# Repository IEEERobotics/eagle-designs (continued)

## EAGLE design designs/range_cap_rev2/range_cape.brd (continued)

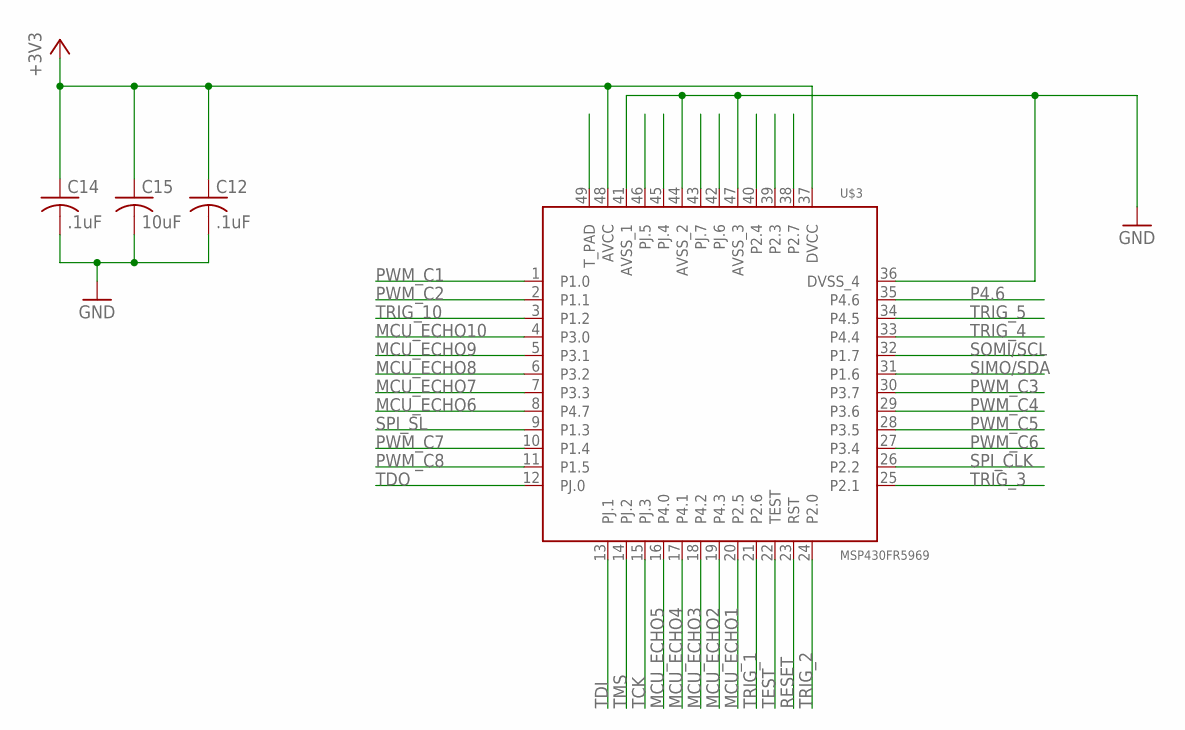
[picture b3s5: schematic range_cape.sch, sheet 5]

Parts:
C12, C14: .1uF; C0805
C15: 10uF; C0805
U$3: MSP430FR5969; QFN50P700X700X100-49N

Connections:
+3V3: C12.1, C14.1, C15.1, U$3.37 (DVCC), U$3.48 (AVCC); also elsewhere on the board
GND: C12.2, C14.2, C15.2, U$3.36 (DVSS_4), U$3.41 (AVSS_1), U$3.44 (AVSS_2), U$3.47 (AVSS_3); also elsewhere on the board
MCU_ECHO1: U$3.20 (P2.5); also elsewhere on the board
MCU_ECHO2: U$3.19 (P4.3); also elsewhere on the board
MCU_ECHO3: U$3.18 (P4.2); also elsewhere on the board
MCU_ECHO4: U$3.17 (P4.1); also elsewhere on the board
MCU_ECHO5: U$3.16 (P4.0); also elsewhere on the board
MCU_ECHO6: U$3.8 (P4.7); also elsewhere on the board
MCU_ECHO7: U$3.7 (P3.3); also elsewhere on the board
MCU_ECHO8: U$3.6 (P3.2); also elsewhere on the board
MCU_ECHO9: U$3.5 (P3.1); also elsewhere on the board
MCU_ECHO10: U$3.4 (P3.0); also elsewhere on the board
P2.3: U$3.39 (P2.3)
P2.4: U$3.40 (P2.4)
P2.7: U$3.38 (P2.7)
P4.6: U$3.35 (P4.6)
PWM_C1: U$3.1 (P1.0); also elsewhere on the board
PWM_C2: U$3.2 (P1.1); also elsewhere on the board
PWM_C3: U$3.30 (P3.7); also elsewhere on the board
PWM_C4: U$3.29 (P3.6); also elsewhere on the board
PWM_C5: U$3.28 (P3.5); also elsewhere on the board
PWM_C6: U$3.27 (P3.4); also elsewhere on the board
PWM_C7: U$3.10 (P1.4); also elsewhere on the board
PWM_C8: U$3.11 (P1.5); also elsewhere on the board
RESET: U$3.23 (RST); also elsewhere on the board
SIMO/SDA: U$3.31 (P1.6); also elsewhere on the board
SOMI/SCL: U$3.32 (P1.7); also elsewhere on the board
SPI_CLK: U$3.26 (P2.2); also elsewhere on the board
SPI_SL: U$3.9 (P1.3); also elsewhere on the board
TCK: U$3.15 (PJ.3); also elsewhere on the board
TDI: U$3.13 (PJ.1); also elsewhere on the board
TDO: U$3.12 (PJ.0); also elsewhere on the board
TEST: U$3.22 (TEST); also elsewhere on the board
TMS: U$3.14 (PJ.2); also elsewhere on the board
TRIG_1: U$3.21 (P2.6); also elsewhere on the board
TRIG_2: U$3.24 (P2.0); also elsewhere on the board
TRIG_3: U$3.25 (P2.1); also elsewhere on the board
TRIG_4: U$3.33 (P4.4); also elsewhere on the board
TRIG_5: U$3.34 (P4.5); also elsewhere on the board
TRIG_6: U$3.42 (PJ.6); also elsewhere on the board
TRIG_7: U$3.43 (PJ.7); also elsewhere on the board
TRIG_8: U$3.45 (PJ.4); also elsewhere on the board
TRIG_9: U$3.46 (PJ.5); also elsewhere on the board
TRIG_10: U$3.3 (P1.2); also elsewhere on the board
T_PAD: U$3.49 (T_PAD)

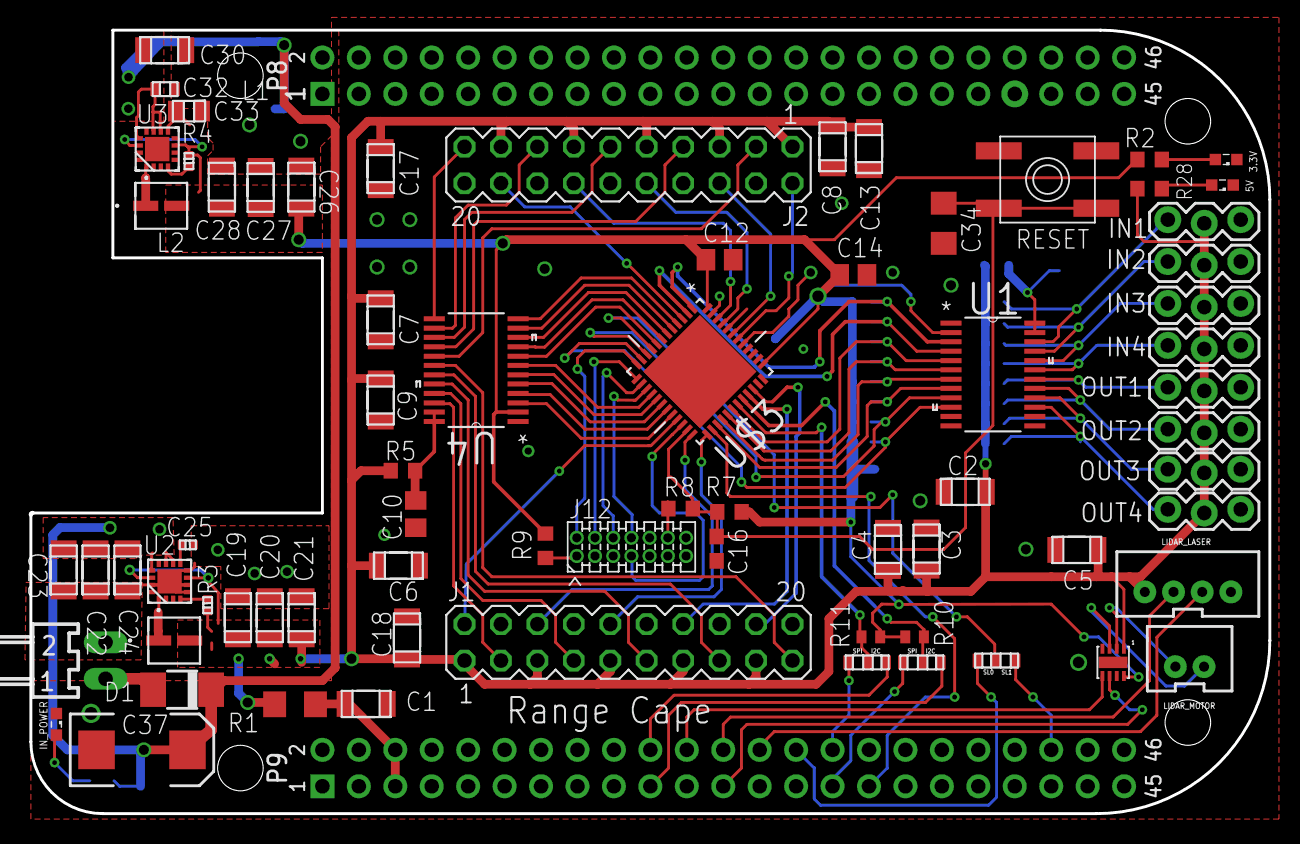
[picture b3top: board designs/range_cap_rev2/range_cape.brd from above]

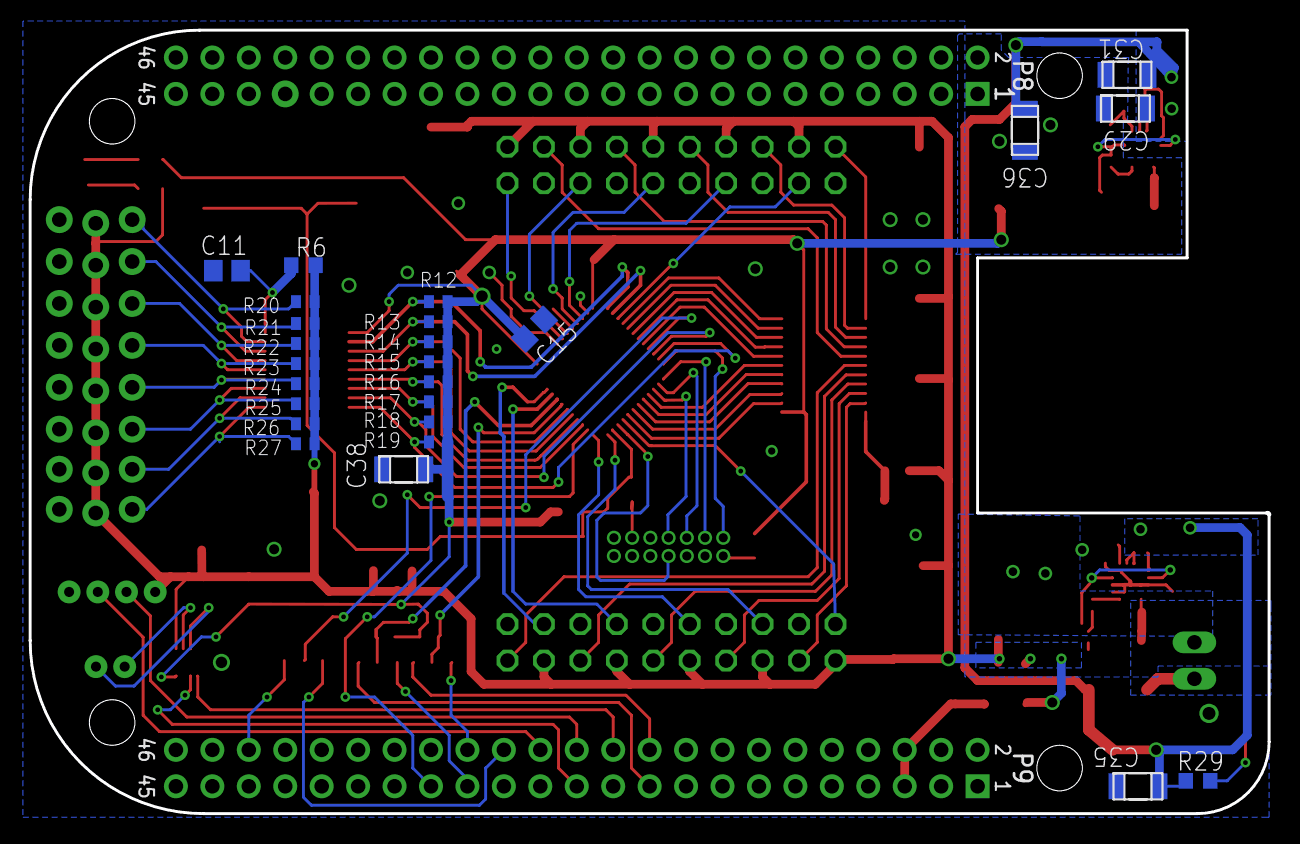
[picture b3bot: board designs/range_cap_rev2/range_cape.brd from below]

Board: 2 copper layers, 86.4 x 54.6 mm, 97 parts (25 on the bottom side), 87 nets.

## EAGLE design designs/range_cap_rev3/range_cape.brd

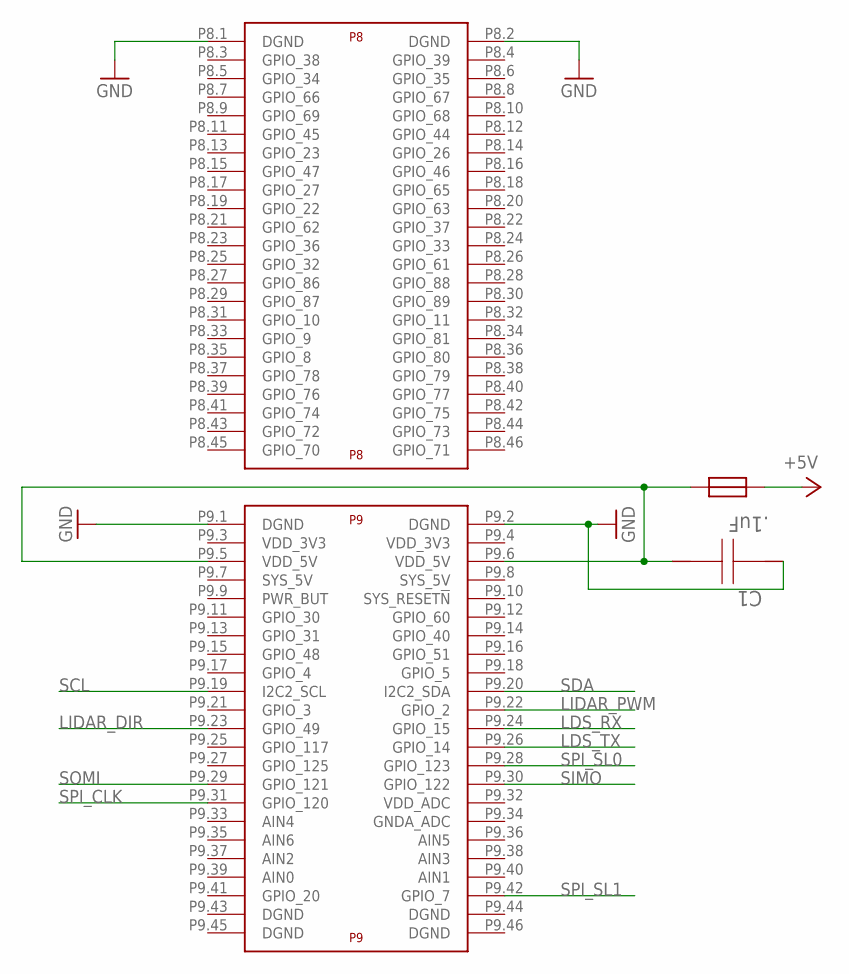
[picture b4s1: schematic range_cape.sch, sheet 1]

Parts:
C1: .1uF; 1206
U$1: BEAGLE_BONE_BLACK_CAPE
U$11: NANO_FUSE

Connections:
+5V: U$11.2; also elsewhere on the board
GND: C1.2, U$1.P8.1 (DGND), U$1.P8.2 (DGND), U$1.P9.1 (DGND), U$1.P9.2 (DGND); also elsewhere on the board
LDS_RX: U$1.P9.24 (GPIO_15); also elsewhere on the board
LDS_TX: U$1.P9.26 (GPIO_14); also elsewhere on the board
LIDAR_DIR: U$1.P9.23 (GPIO_49); also elsewhere on the board
LIDAR_PWM: U$1.P9.22 (GPIO_2); also elsewhere on the board
unnamed: C1.1, U$1.P9.5 (VDD_5V), U$1.P9.6 (VDD_5V), U$11.1
SCL: U$1.P9.19 (I2C2_SCL); also elsewhere on the board
SDA: U$1.P9.20 (I2C2_SDA); also elsewhere on the board
SIMO: U$1.P9.30 (GPIO_122); also elsewhere on the board
SOMI: U$1.P9.29 (GPIO_121); also elsewhere on the board
SPI_CLK: U$1.P9.31 (GPIO_120); also elsewhere on the board
SPI_SL0: U$1.P9.28 (GPIO_123); also elsewhere on the board
SPI_SL1: U$1.P9.42 (GPIO_7); also elsewhere on the board

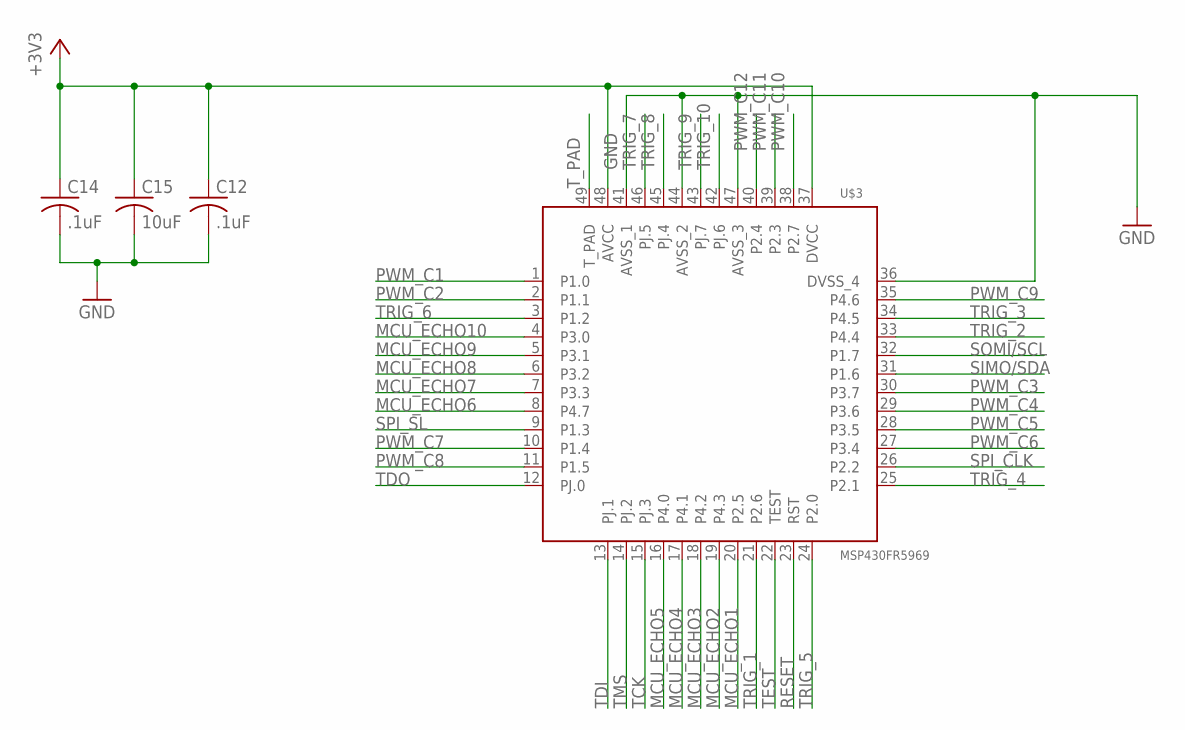
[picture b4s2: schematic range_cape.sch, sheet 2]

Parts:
C12, C14: .1uF; C0805
C15: 10uF; C0805
U$3: MSP430FR5969; QFN50P700X700X100-49N

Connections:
+3V3: C12.1, C14.1, C15.1, U$3.37 (DVCC), U$3.48 (AVCC); also elsewhere on the board
GND: C12.2, C14.2, C15.2, U$3.36 (DVSS_4), U$3.41 (AVSS_1), U$3.44 (AVSS_2), U$3.47 (AVSS_3); also elsewhere on the board
MCU_ECHO1: U$3.20 (P2.5); also elsewhere on the board
MCU_ECHO2: U$3.19 (P4.3); also elsewhere on the board
MCU_ECHO3: U$3.18 (P4.2); also elsewhere on the board
MCU_ECHO4: U$3.17 (P4.1); also elsewhere on the board
MCU_ECHO5: U$3.16 (P4.0); also elsewhere on the board
MCU_ECHO6: U$3.8 (P4.7); also elsewhere on the board
MCU_ECHO7: U$3.7 (P3.3); also elsewhere on the board
MCU_ECHO8: U$3.6 (P3.2); also elsewhere on the board
MCU_ECHO9: U$3.5 (P3.1); also elsewhere on the board
MCU_ECHO10: U$3.4 (P3.0); also elsewhere on the board
PWM_C1: U$3.1 (P1.0); also elsewhere on the board
PWM_C2: U$3.2 (P1.1); also elsewhere on the board
PWM_C3: U$3.30 (P3.7); also elsewhere on the board
PWM_C4: U$3.29 (P3.6); also elsewhere on the board
PWM_C5: U$3.28 (P3.5); also elsewhere on the board
PWM_C6: U$3.27 (P3.4); also elsewhere on the board
PWM_C7: U$3.10 (P1.4); also elsewhere on the board
PWM_C8: U$3.11 (P1.5); also elsewhere on the board
PWM_C9: U$3.35 (P4.6); also elsewhere on the board
PWM_C10: U$3.38 (P2.7); also elsewhere on the board
PWM_C11: U$3.39 (P2.3); also elsewhere on the board
PWM_C12: U$3.40 (P2.4); also elsewhere on the board
RESET: U$3.23 (RST); also elsewhere on the board
SIMO/SDA: U$3.31 (P1.6); also elsewhere on the board
SOMI/SCL: U$3.32 (P1.7); also elsewhere on the board
SPI_CLK: U$3.26 (P2.2); also elsewhere on the board
SPI_SL: U$3.9 (P1.3); also elsewhere on the board
TCK: U$3.15 (PJ.3); also elsewhere on the board
TDI: U$3.13 (PJ.1); also elsewhere on the board
TDO: U$3.12 (PJ.0); also elsewhere on the board
TEST: U$3.22 (TEST); also elsewhere on the board
TMS: U$3.14 (PJ.2); also elsewhere on the board
TRIG_1: U$3.21 (P2.6); also elsewhere on the board
TRIG_2: U$3.33 (P4.4); also elsewhere on the board
TRIG_3: U$3.34 (P4.5); also elsewhere on the board
TRIG_4: U$3.25 (P2.1); also elsewhere on the board
TRIG_5: U$3.24 (P2.0); also elsewhere on the board
TRIG_6: U$3.3 (P1.2); also elsewhere on the board
TRIG_7: U$3.46 (PJ.5); also elsewhere on the board
TRIG_8: U$3.45 (PJ.4); also elsewhere on the board
TRIG_9: U$3.43 (PJ.7); also elsewhere on the board
TRIG_10: U$3.42 (PJ.6); also elsewhere on the board
T_PAD: U$3.49 (T_PAD)

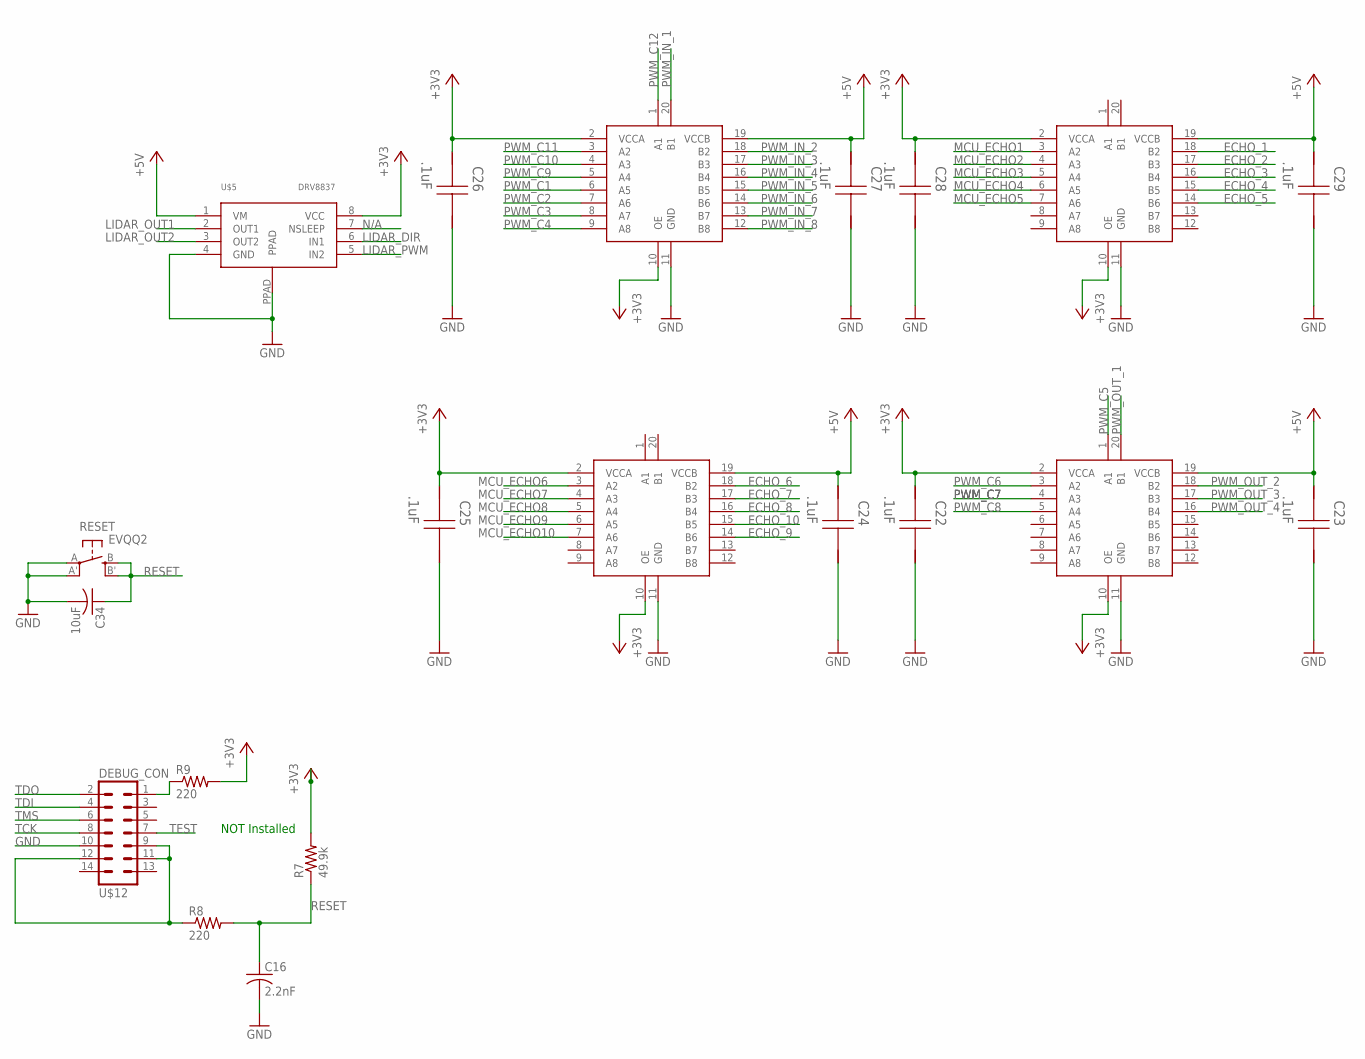
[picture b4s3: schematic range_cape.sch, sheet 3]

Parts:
C16: 2.2nF; C0603
C22, C23, C24, C25, C26, C27, C28, C29: .1uF; 1206
C34: 10uF; C1206
R7: 49.9k; R0603
R8, R9: 220; R0603
RESET: EVQQ2; EVQ-Q2
U$5: DRV8837; WSON-8
U$6, U$7, U$8, U$9: TXB0108; TSSOP-20
U$12: DEBUG_CON; DEBUG_SM

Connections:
+3V3: C22.2, C25.2, C26.2, C28.2, R7.2, R9.2, U$5.8 (VCC), U$6.2 (VCCA), U$6.10 (OE), U$7.2 (VCCA), U$7.10 (OE), U$8.2 (VCCA), U$8.10 (OE), U$9.2 (VCCA), U$9.10 (OE); also elsewhere on the board
+5V: C23.2, C24.2, C27.2, C29.2, U$5.1 (VM), U$6.19 (VCCB), U$7.19 (VCCB), U$8.19 (VCCB), U$9.19 (VCCB); also elsewhere on the board
ECHO_1: U$6.18 (B2); also elsewhere on the board
ECHO_2: U$6.17 (B3); also elsewhere on the board
ECHO_3: U$6.16 (B4); also elsewhere on the board
ECHO_4: U$6.15 (B5); also elsewhere on the board
ECHO_5: U$6.14 (B6); also elsewhere on the board
ECHO_6: U$8.18 (B2); also elsewhere on the board
ECHO_7: U$8.17 (B3); also elsewhere on the board
ECHO_8: U$8.16 (B4); also elsewhere on the board
ECHO_9: U$8.14 (B6); also elsewhere on the board
ECHO_10: U$8.15 (B5); also elsewhere on the board
GND: C16.2, C22.1, C23.1, C24.1, C25.1, C26.1, C27.1, C28.1, C29.1, C34.2, RESET.A, RESET.A' (P1), U$5.4 (GND), U$5.PPAD, U$6.11 (GND), U$7.11 (GND), U$8.11 (GND), U$9.11 (GND), U$12.10; also elsewhere on the board
LIDAR_DIR: U$5.6 (IN1); also elsewhere on the board
LIDAR_OUT1: U$5.2 (OUT1); also elsewhere on the board
LIDAR_OUT2: U$5.3 (OUT2); also elsewhere on the board
LIDAR_PWM: U$5.5 (IN2); also elsewhere on the board
MCU_ECHO1: U$6.3 (A2); also elsewhere on the board
MCU_ECHO2: U$6.4 (A3); also elsewhere on the board
MCU_ECHO3: U$6.5 (A4); also elsewhere on the board
MCU_ECHO4: U$6.6 (A5); also elsewhere on the board
MCU_ECHO5: U$6.7 (A6); also elsewhere on the board
MCU_ECHO6: U$8.3 (A2); also elsewhere on the board
MCU_ECHO7: U$8.4 (A3); also elsewhere on the board
MCU_ECHO8: U$8.5 (A4); also elsewhere on the board
MCU_ECHO9: U$8.6 (A5); also elsewhere on the board
MCU_ECHO10: U$8.7 (A6); also elsewhere on the board
unnamed: R8.1, U$12.9, U$12.11, U$12.12
unnamed: R9.1, U$12.1
N/A: U$5.7 (NSLEEP)
PWM_C1: U$9.6 (A5); also elsewhere on the board
PWM_C2: U$9.7 (A6); also elsewhere on the board
PWM_C3: U$9.8 (A7); also elsewhere on the board
PWM_C4: U$9.9 (A8); also elsewhere on the board
PWM_C5: U$7.1 (A1); also elsewhere on the board
PWM_C6: U$7.3 (A2); also elsewhere on the board
PWM_C7: U$7.4 (A3); also elsewhere on the board
PWM_C8: U$7.5 (A4); also elsewhere on the board
PWM_C9: U$9.5 (A4); also elsewhere on the board
PWM_C10: U$9.4 (A3); also elsewhere on the board
PWM_C11: U$9.3 (A2); also elsewhere on the board
PWM_C12: U$9.1 (A1); also elsewhere on the board
PWM_IN_1: U$9.20 (B1); also elsewhere on the board
PWM_IN_2: U$9.18 (B2); also elsewhere on the board
PWM_IN_3: U$9.17 (B3); also elsewhere on the board
PWM_IN_4: U$9.16 (B4); also elsewhere on the board
PWM_IN_5: U$9.15 (B5); also elsewhere on the board
PWM_IN_6: U$9.14 (B6); also elsewhere on the board
PWM_IN_7: U$9.13 (B7); also elsewhere on the board
PWM_IN_8: U$9.12 (B8); also elsewhere on the board
PWM_OUT_1: U$7.20 (B1); also elsewhere on the board
PWM_OUT_2: U$7.18 (B2); also elsewhere on the board
PWM_OUT_3: U$7.17 (B3); also elsewhere on the board
PWM_OUT_4: U$7.16 (B4); also elsewhere on the board
RESET: C16.1, C34.1, R7.1, R8.2, RESET.B (S), RESET.B' (S1); also elsewhere on the board
TCK: U$12.8; also elsewhere on the board
TDI: U$12.4; also elsewhere on the board
TDO: U$12.2; also elsewhere on the board
TEST: U$12.7; also elsewhere on the board
TMS: U$12.6; also elsewhere on the board

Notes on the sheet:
NOT Installed

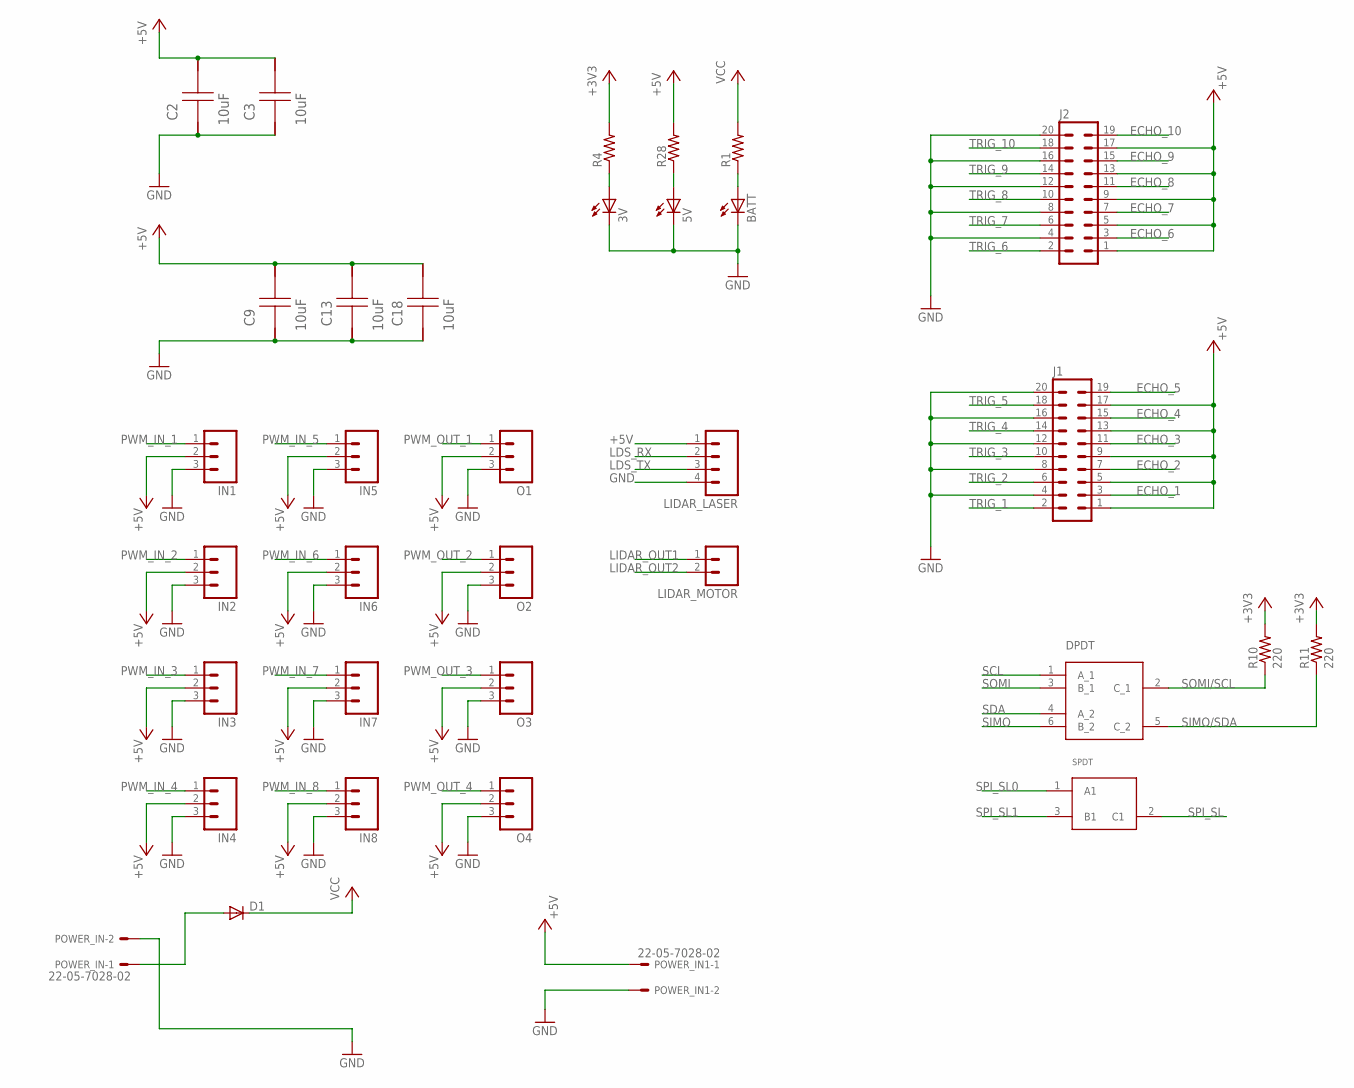
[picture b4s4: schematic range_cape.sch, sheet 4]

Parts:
3V, 5V: LED_ESML0603; LED_SML0603
BATT: LED_ESML0603; LED_SML0603
C2, C3, C9, C13, C18: 10uF; 1206
D1: DIODE-DO-214AC; DO-214AC
IN1, IN2, IN3, IN4, IN5, IN6, IN7, IN8: M03LOCK; 1X03_LOCK
J1, J2: MA10-2
LIDAR_LASER: M04JST-PTH-VERT; JST-4-PTH-VERT
LIDAR_MOTOR: M02JST-PTH-VERT; JST-2-PTH-VERT
O1, O2, O3, O4: M03LOCK; 1X03_LOCK
POWER_IN, POWER_IN1: 22-05-7028-02; 7395-02
R1, R4, R28: R-US_R0603; R0603
R10, R11: 220; R0402
SPDT: SPDT_SWITCH; SPDT
U$4: DPDT_I2C_SPI; DPDT

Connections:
+3V3: R4.2, R10.2, R11.2; also elsewhere on the board
+5V: C2.1, C3.1, C9.1, C13.1, C18.1, IN1.2, IN2.2, IN3.2, IN4.2, IN5.2, IN6.2, IN7.2, IN8.2, J1.1, J1.5, J1.9, J1.13, J1.17, J2.1, J2.5, J2.9, J2.13, J2.17, LIDAR_LASER.1, O1.2, O2.2, O3.2, O4.2, POWER_IN1.1, R28.2; also elsewhere on the board
ECHO_1: J1.3; also elsewhere on the board
ECHO_2: J1.7; also elsewhere on the board
ECHO_3: J1.11; also elsewhere on the board
ECHO_4: J1.15; also elsewhere on the board
ECHO_5: J1.19; also elsewhere on the board
ECHO_6: J2.3; also elsewhere on the board
ECHO_7: J2.7; also elsewhere on the board
ECHO_8: J2.11; also elsewhere on the board
ECHO_9: J2.15; also elsewhere on the board
ECHO_10: J2.19; also elsewhere on the board
GND: 3V.C, 5V.C, BATT.C, C2.2, C3.2, C9.2, C13.2, C18.2, IN1.3, IN2.3, IN3.3, IN4.3, IN5.3, IN6.3, IN7.3, IN8.3, J1.4, J1.8, J1.12, J1.16, J1.20, J2.4, J2.8, J2.12, J2.16, J2.20, LIDAR_LASER.4, O1.3, O2.3, O3.3, O4.3, POWER_IN.2, POWER_IN1.2; also elsewhere on the board
LDS_RX: LIDAR_LASER.2; also elsewhere on the board
LDS_TX: LIDAR_LASER.3; also elsewhere on the board
LIDAR_OUT1: LIDAR_MOTOR.1; also elsewhere on the board
LIDAR_OUT2: LIDAR_MOTOR.2; also elsewhere on the board
unnamed: D1.A, POWER_IN.1
unnamed: BATT.A, R1.1
unnamed: 3V.A, R4.1
unnamed: 5V.A, R28.1
PWM_IN_1: IN1.1; also elsewhere on the board
PWM_IN_2: IN2.1; also elsewhere on the board
PWM_IN_3: IN3.1; also elsewhere on the board
PWM_IN_4: IN4.1; also elsewhere on the board
PWM_IN_5: IN5.1; also elsewhere on the board
PWM_IN_6: IN6.1; also elsewhere on the board
PWM_IN_7: IN7.1; also elsewhere on the board
PWM_IN_8: IN8.1; also elsewhere on the board
PWM_OUT_1: O1.1; also elsewhere on the board
PWM_OUT_2: O2.1; also elsewhere on the board
PWM_OUT_3: O3.1; also elsewhere on the board
PWM_OUT_4: O4.1; also elsewhere on the board
SCL: U$4.1 (A_1); also elsewhere on the board
SDA: U$4.4 (A_2); also elsewhere on the board
SIMO: U$4.6 (B_2); also elsewhere on the board
SIMO/SDA: R11.1, U$4.5 (C_2); also elsewhere on the board
SOMI: U$4.3 (B_1); also elsewhere on the board
SOMI/SCL: R10.1, U$4.2 (C_1); also elsewhere on the board
SPI_SL: SPDT.2 (C1); also elsewhere on the board
SPI_SL0: SPDT.1 (A1); also elsewhere on the board
SPI_SL1: SPDT.3 (B1); also elsewhere on the board
TRIG_1: J1.2; also elsewhere on the board
TRIG_2: J1.6; also elsewhere on the board
TRIG_3: J1.10; also elsewhere on the board
TRIG_4: J1.14; also elsewhere on the board
TRIG_5: J1.18; also elsewhere on the board
TRIG_6: J2.2; also elsewhere on the board
TRIG_7: J2.6; also elsewhere on the board
TRIG_8: J2.10; also elsewhere on the board
TRIG_9: J2.14; also elsewhere on the board
TRIG_10: J2.18; also elsewhere on the board
VCC: D1.C, R1.2; also elsewhere on the board

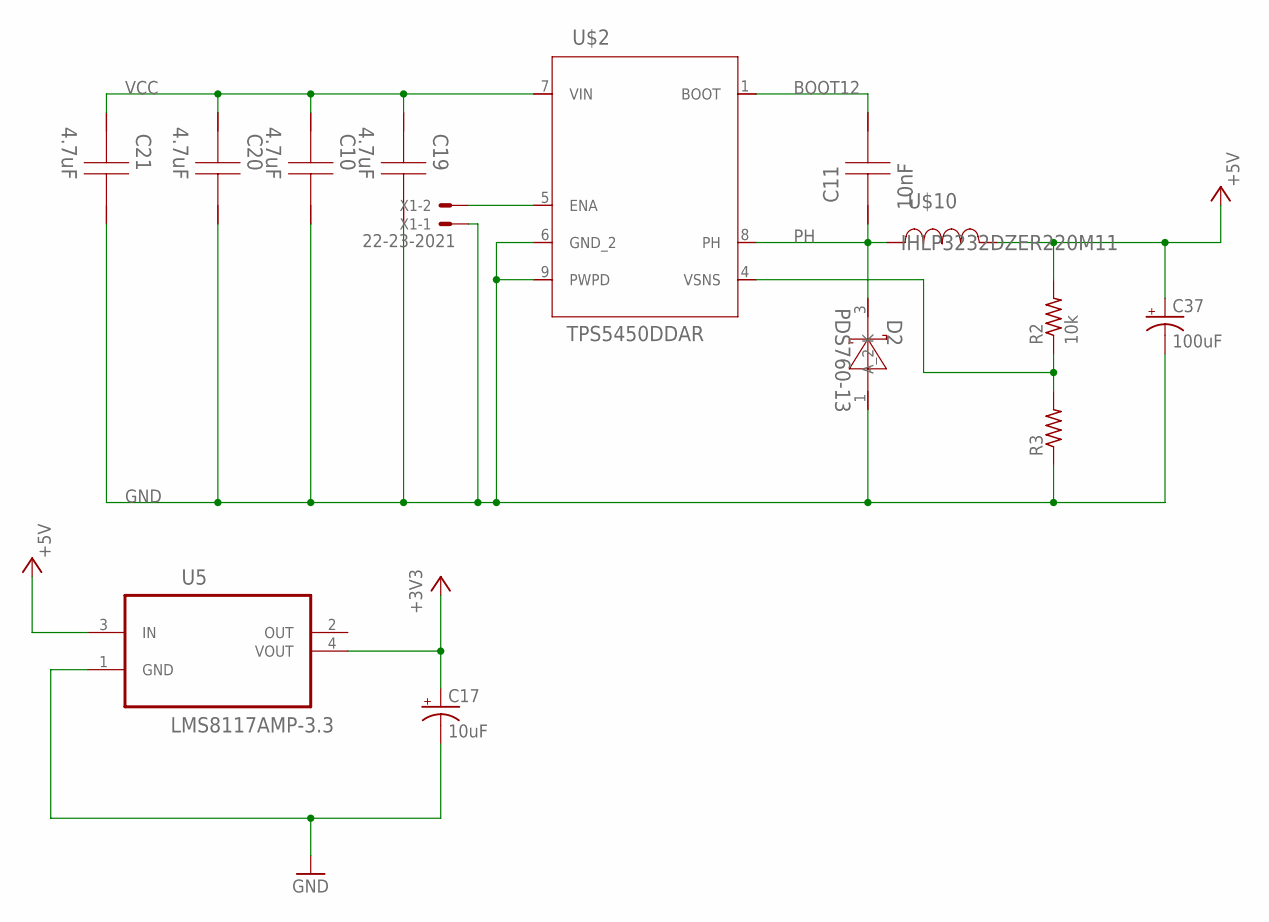
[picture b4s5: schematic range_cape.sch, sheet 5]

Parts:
C10, C19, C20, C21: 4.7uF; 1206
C11: 10nF; 0805
C17: 10uF; EIA3216
C37: 100uF; EIA7343
D2: PDS760-13; POWERDI5
R2: 10k; M0805
R3: R-US_M0805; M0805
U5: LMS8117AMP-3.3; SOT230P696X180-4N
U$2: TPS5450DDAR; R-PDSO-G8
U$10: IHLP3232DZER220M11; IHLP-3232DZ
X1: 22-23-2021

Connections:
+3V3: C17.A (+), U5.4 (VOUT); also elsewhere on the board
+5V: C37.A (+), R2.2, U5.3 (IN), U$10.2; also elsewhere on the board
BOOT12: C11.1, U$2.1 (BOOT)
GND: C10.1, C17.C (-), C19.1, C20.1, C21.1, C37.C (-), D2.1 (A_2), R3.1, U5.1 (GND), U$2.6 (GND_2), U$2.9 (PWPD), X1.1; also elsewhere on the board
unnamed: U$2.5 (ENA), X1.2
PH: C11.2, D2.3 (K), U$2.8 (PH), U$10.1
VCC: C10.2, C19.2, C20.2, C21.2, U$2.7 (VIN); also elsewhere on the board
VSNS12: R2.1, R3.2, U$2.4 (VSNS)

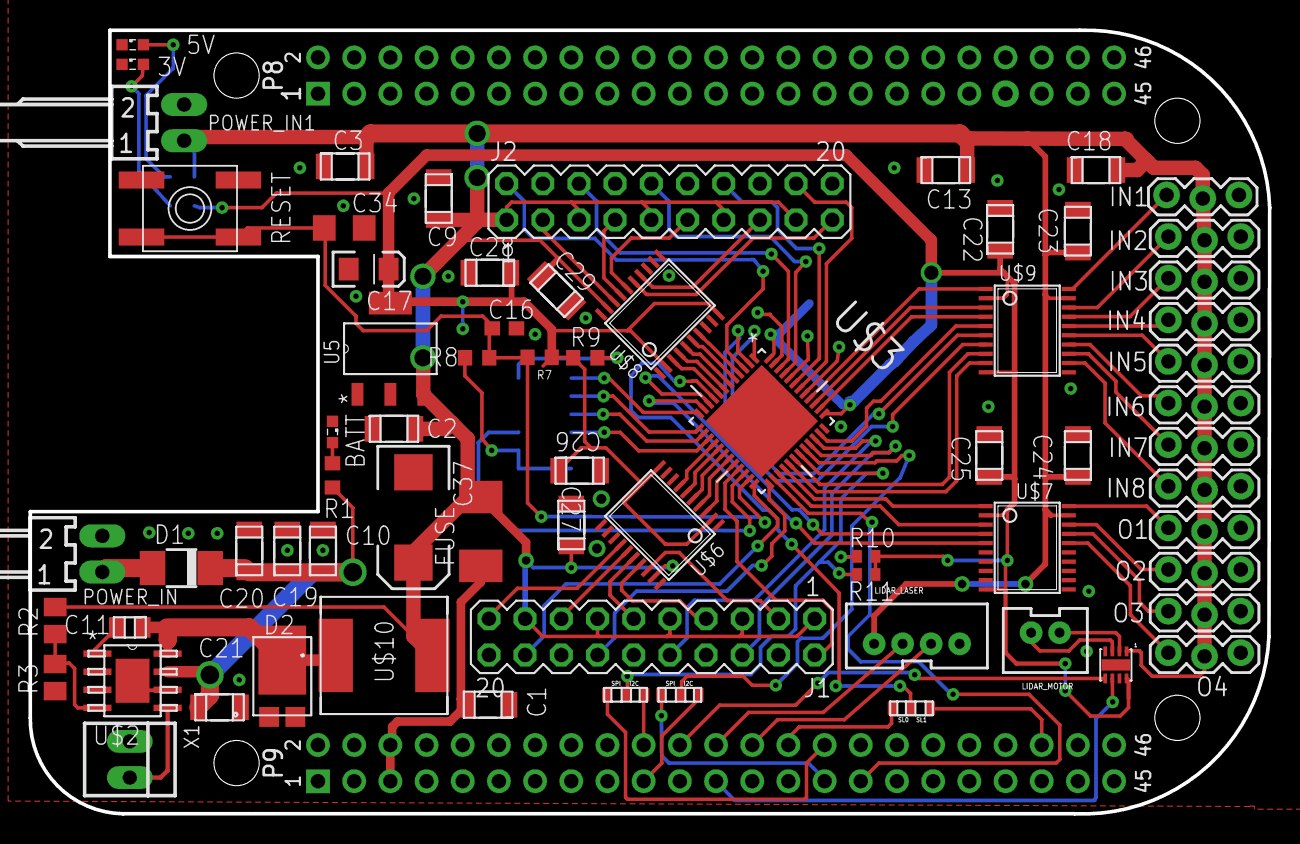
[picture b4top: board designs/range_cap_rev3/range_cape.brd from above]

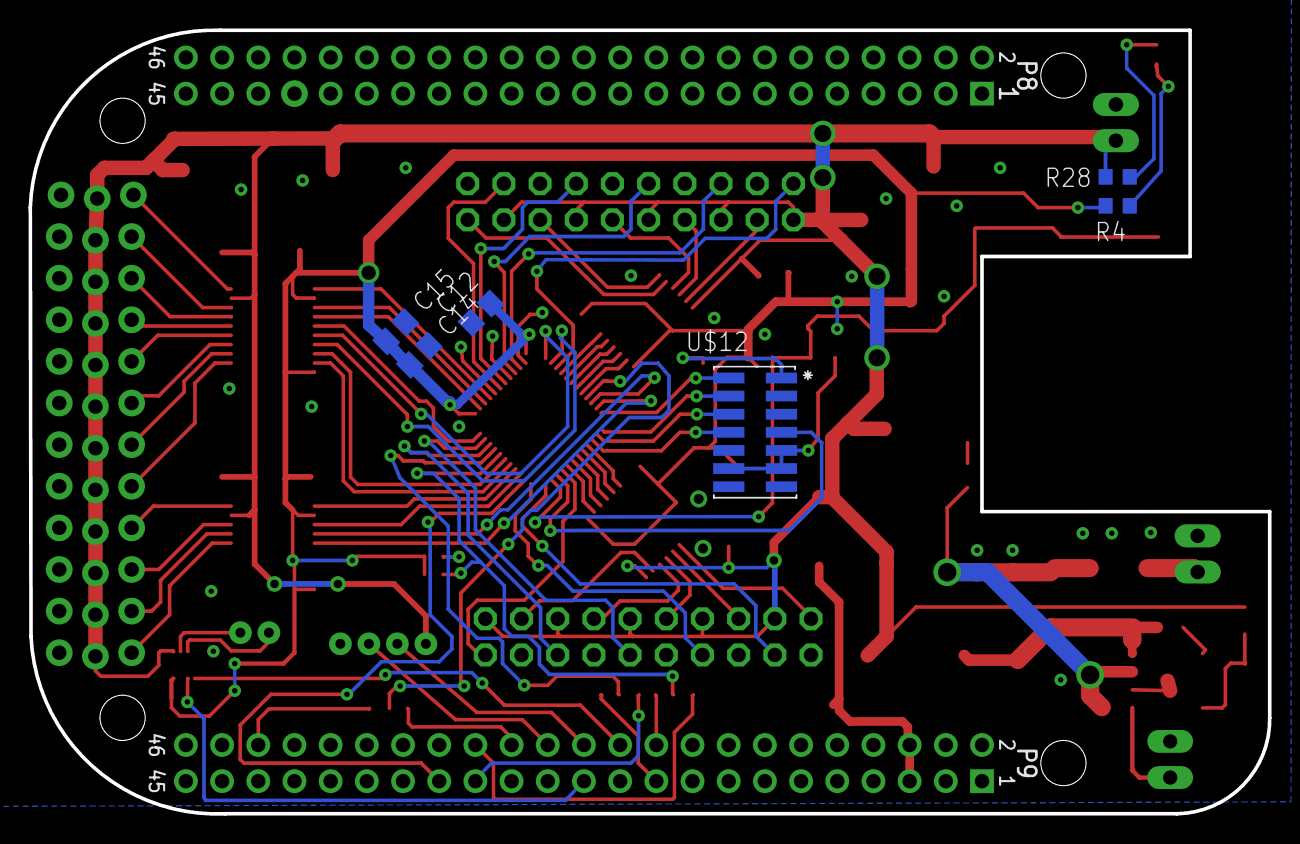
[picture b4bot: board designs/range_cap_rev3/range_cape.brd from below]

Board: 2 copper layers, 87.0 x 55.0 mm, 75 parts (6 on the bottom side), 91 nets.

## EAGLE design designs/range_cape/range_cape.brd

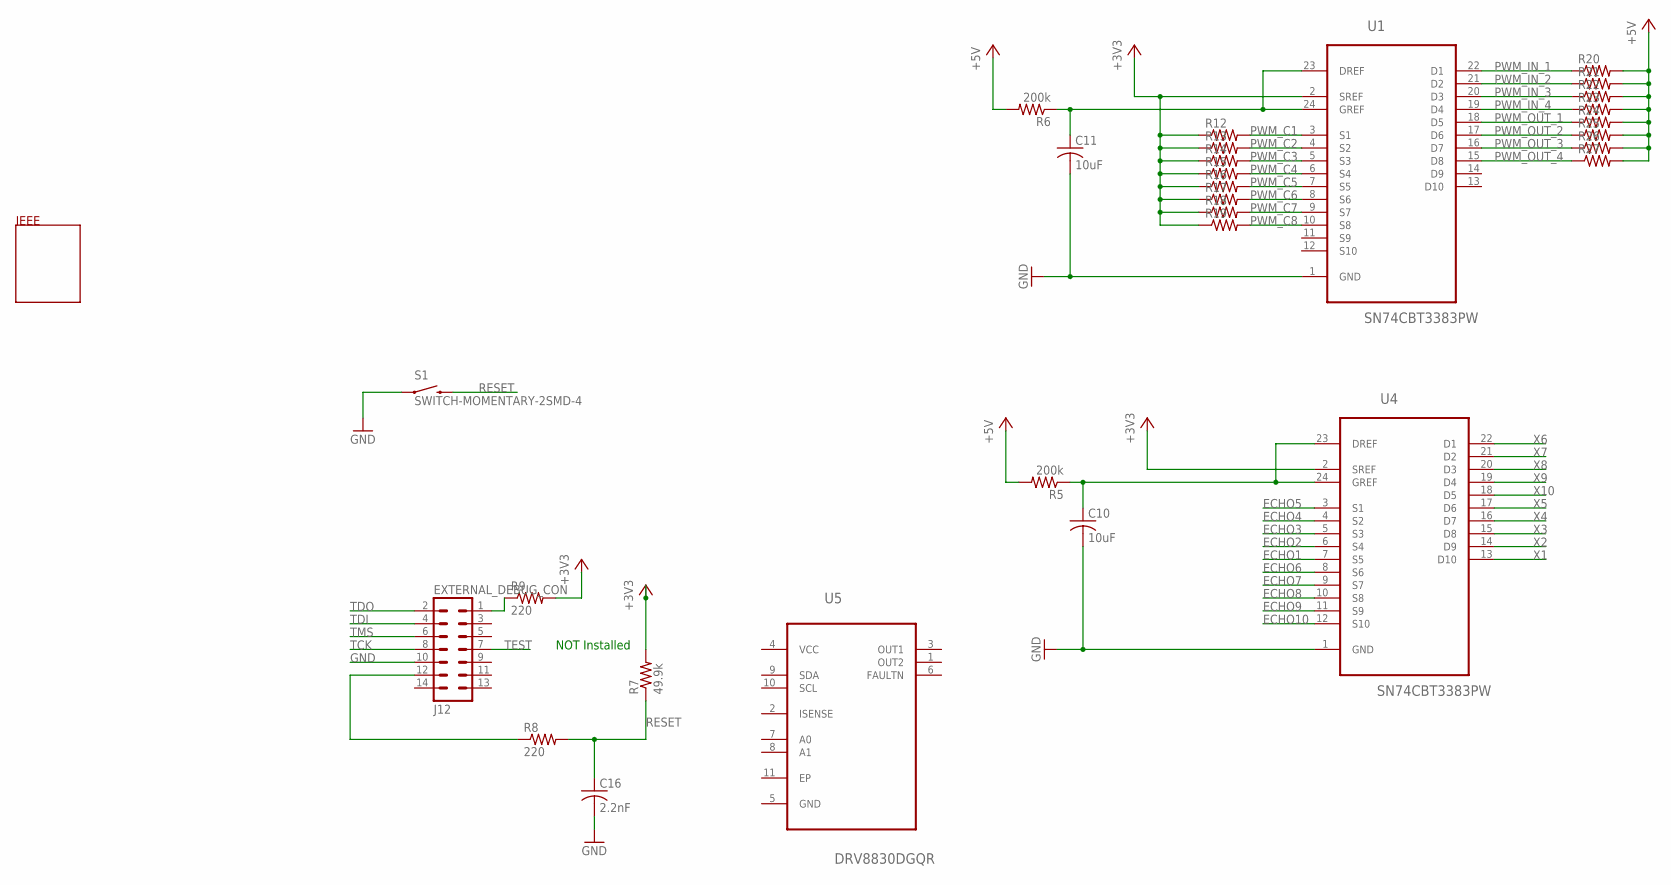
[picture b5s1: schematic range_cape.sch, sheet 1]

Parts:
C10, C11: 10uF; C0805
C16: 2.2nF; C0603
J12: EXTERNAL_DEBUG_CON; EXTERNAL_DEBUG
R5, R6: 200k; R0603
R7: 49.9k; R0603
R8, R9: 220; R0603
R12, R13, R14, R15, R16, R17, R18, R19, R20, R21, R22, R23, R24, R25, R26, R27: R-US_R0402; R0402
S1: SWITCH-MOMENTARY-2SMD-4; TACTILE_SWITCH_TALL
U1, U4: SN74CBT3383PW; SOP65P640X120-24N
U5: DRV8830DGQR; SOP65P640X110-15N
U$2: IEEE

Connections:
+3V3: R7.2, R9.2, R12.1, R13.1, R14.1, R15.1, R16.1, R17.1, R18.1, R19.1, U1.2 (SREF), U4.2 (SREF); also elsewhere on the board
+5V: R5.2, R6.2, R20.2, R21.2, R22.2, R23.2, R24.2, R25.2, R26.2, R27.2; also elsewhere on the board
ECHO1: U4.7 (S5)
ECHO2: U4.6 (S4)
ECHO3: U4.5 (S3)
ECHO4: U4.4 (S2)
ECHO5: U4.3 (S1)
ECHO6: U4.8 (S6)
ECHO7: U4.9 (S7)
ECHO8: U4.10 (S8)
ECHO9: U4.11 (S9)
ECHO10: U4.12 (S10)
GND: C10.2, C11.2, C16.2, J12.10, S1.A2 (1), U1.1 (GND), U4.1 (GND); also elsewhere on the board
unnamed: C11.1, R6.1, U1.23 (DREF), U1.24 (GREF)
unnamed: J12.12, R8.1
unnamed: J12.1, R9.1
unnamed: C10.1, R5.1, U4.23 (DREF), U4.24 (GREF)
PWM_C1: R12.2, U1.3 (S1)
PWM_C2: R13.2, U1.4 (S2)
PWM_C3: R14.2, U1.5 (S3)
PWM_C4: R15.2, U1.6 (S4)
PWM_C5: R16.2, U1.7 (S5)
PWM_C6: R17.2, U1.8 (S6)
PWM_C7: R18.2, U1.9 (S7)
PWM_C8: R19.2, U1.10 (S8)
PWM_IN_1: R20.1, U1.22 (D1); also elsewhere on the board
PWM_IN_2: R21.1, U1.21 (D2); also elsewhere on the board
PWM_IN_3: R22.1, U1.20 (D3); also elsewhere on the board
PWM_IN_4: R23.1, U1.19 (D4); also elsewhere on the board
PWM_OUT_1: R24.1, U1.18 (D5); also elsewhere on the board
PWM_OUT_2: R25.1, U1.17 (D6); also elsewhere on the board
PWM_OUT_3: R26.1, U1.16 (D7); also elsewhere on the board
PWM_OUT_4: R27.1, U1.15 (D8); also elsewhere on the board
RESET: C16.1, R7.1, R8.2, S1.B2 (2)
TCK: J12.8
TDI: J12.4
TDO: J12.2
TEST: J12.7
TMS: J12.6
VCC: U5.4 (VCC); also elsewhere on the board
X1: U4.13 (D10); also elsewhere on the board
X2: U4.14 (D9); also elsewhere on the board
X3: U4.15 (D8); also elsewhere on the board
X4: U4.16 (D7); also elsewhere on the board
X5: U4.17 (D6); also elsewhere on the board
X6: U4.22 (D1); also elsewhere on the board
X7: U4.21 (D2); also elsewhere on the board
X8: U4.20 (D3); also elsewhere on the board
X9: U4.19 (D4); also elsewhere on the board
X10: U4.18 (D5); also elsewhere on the board

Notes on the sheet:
NOT Installed
